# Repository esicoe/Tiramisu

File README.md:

# Tiramisu: a 1000 Hz Hall-effect osu! tablet

Tiramisu is a drawing tablet for [osu!](https://osu.ppy.sh) that tracks a magnet-tipped pen with a grid of
120 Hall-effect sensors and reports its position over USB **1000 times a second**. That's the USB Full-Speed
ceiling, and 7.5x the 133 Hz of a Wacom CTL-472.

It's my independent prototype of the Hall-effect tablet we're building at
[Wonkle](https://github.com/wonkleio). The board and firmware go by **aim1k** in the source.

## Status

| Board | State |
|---|---|
| `tiramisu-dev-RP2354B` | Fabricated and assembled by JLCPCB, brought up, tracking a magnetic pen |
| `tiramisu-dev-CH32V307` | Next revision, in part selection: a RISC-V MCU with built-in USB 2.0 High-Speed to go past 1 kHz |

## Hardware: `tiramisu-dev-RP2354B`

| | |
|---|---|
| MCU | Raspberry Pi RP2354B (dual Arm Cortex-M33, 2 MB in-package flash) |
| Sensors | 120 x HAL403 linear Hall sensors in a 12 x 10 grid at 10 mm pitch |
| Multiplexing | 8 x CD74HC4067 16:1 analog muxes on a shared select bus, one per ADC input |
| PCB | 4 layers, 154 x 147 mm, designed in KiCad |
| Interface | USB-C (Full-Speed): HID plus an optional CDC debug console. SWD header for debugging |

## How it works

- **Scan (core 1).** DMA-driven round-robin over all 120 sensors at about 1.8 kHz per full frame, keeping a
  baseline and a noise sigma for every sensor. A warm-up conversion pass removes the crosstalk that the
  multiplexers' on-resistance causes in the ADC's sample-and-hold.
- **Solve (core 0).** Detects the pen from per-sensor noise thresholds and spatial coherence, seeds a position
  from the centroid, then refines x, y and hover height with a Levenberg-Marquardt fit of a magnetic dipole. A
  1-Euro filter smooths the output without adding lag during fast flicks.
- **Report.** 1 kHz USB HID, paced by the host's polling. The device exposes two collections: an absolute mouse
  that works with no driver, and a vendor-defined collection for [OpenTabletDriver](https://opentabletdriver.net).

The [firmware README](tiramisu-dev-RP2354B/firmware/README.md) covers the solver, the tuning decisions and how
to test without hardware. The [sensing calculations](tiramisu-dev-RP2354B/docs/CALCULATIONS.md) cover grid
geometry, scan-rate budget and magnet choice.

## Repository layout

```
tiramisu-dev-RP2354B/
  pcb/               KiCad project: schematic and 4-layer layout
  manufacturing/     Gerbers, BOM and pick-and-place files for JLCPCB
  firmware/          C firmware on the Pico SDK and TinyUSB
  scripts/           Python host tools
  opentabletdriver/  OpenTabletDriver tablet config and report parser
  docs/              Sensing and scan-rate calculations
  datasheets/
tiramisu-dev-CH32V307/   Next revision (datasheets so far)
images/                  Photos and renders for this README
```

## Build and flash

The build uses the Raspberry Pi Pico SDK. The Pico VS Code extension installs the SDK, the Arm toolchain, CMake
and Ninja in one go.

```powershell
cd tiramisu-dev-RP2354B/firmware
.\build.ps1           # configure (first time) and build
.\build.ps1 -Clean    # wipe build/ and reconfigure
```

Hold **BOOTSEL**, plug the board in, and copy `build/aim1k.uf2` onto the drive that appears.

## Host tools

All of these are Python 3 with no third-party packages. The USB tools use Windows APIs.

| Script | What it does |
|---|---|
| `scripts/grid_view.py` | Live heatmap of the sensor grid over the debug console, plus noise, raw, baseline and recalibrate views |
| `scripts/rate_test.py` | Measures the real HID report rate and its jitter at the host |
| `scripts/set_mode.py` | Turns the driverless mouse collection on or off |
| `scripts/gen_sensor_map.py` | Regenerates the firmware's sensor map straight from the KiCad PCB |

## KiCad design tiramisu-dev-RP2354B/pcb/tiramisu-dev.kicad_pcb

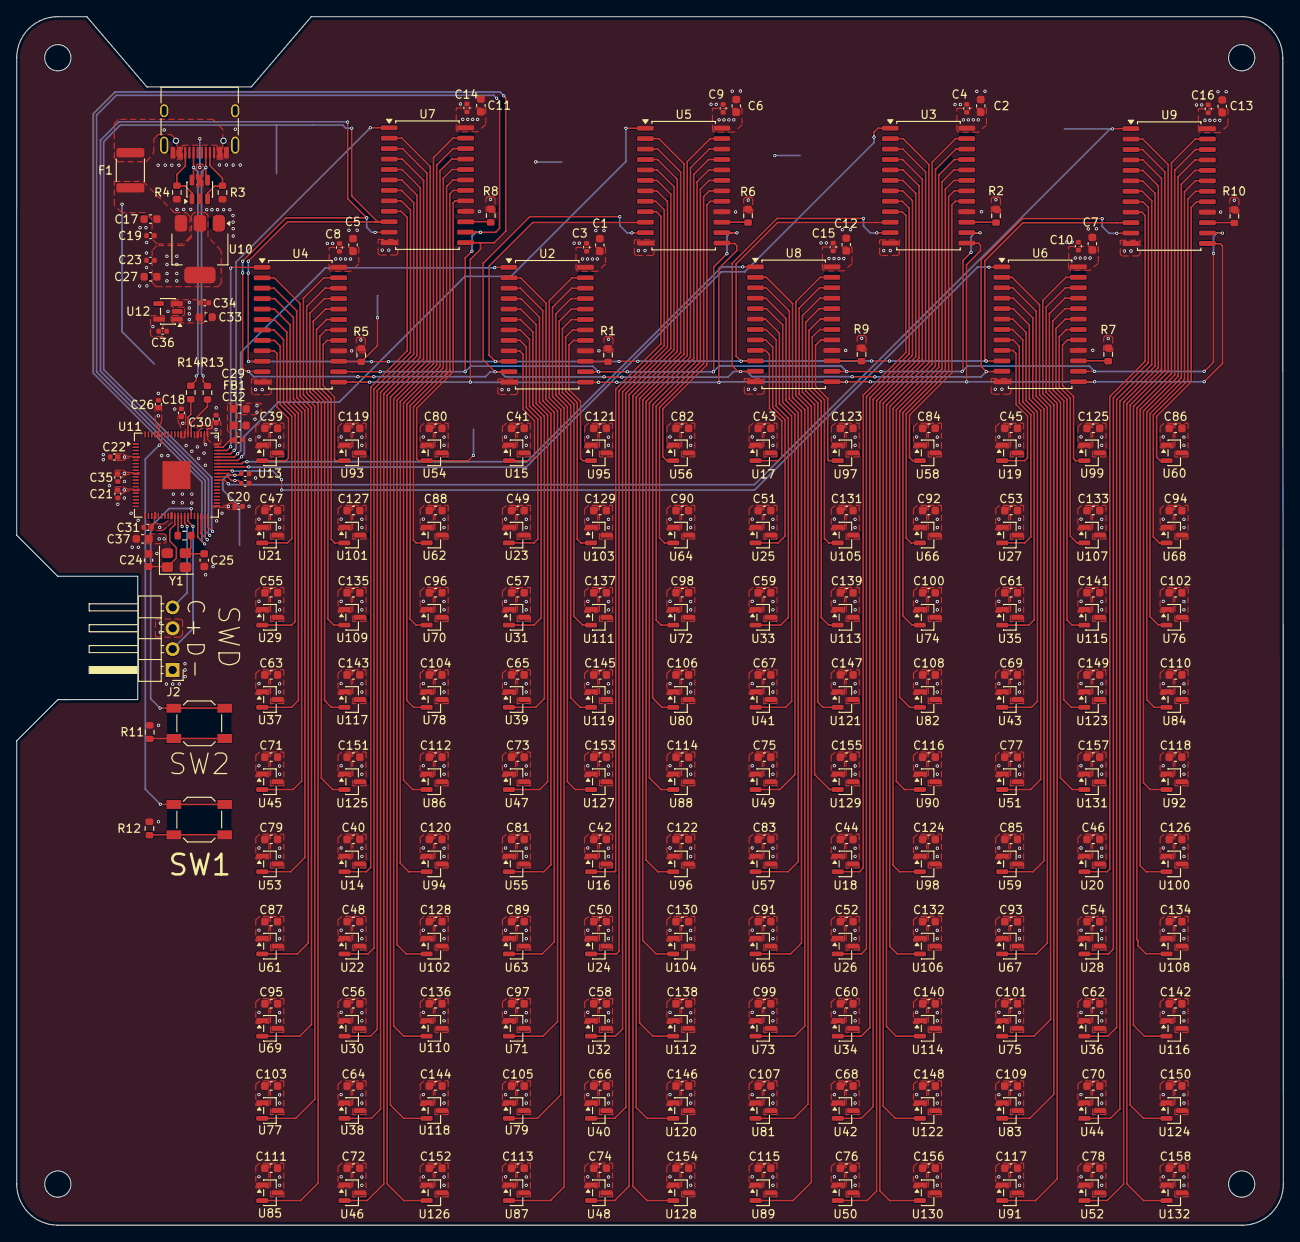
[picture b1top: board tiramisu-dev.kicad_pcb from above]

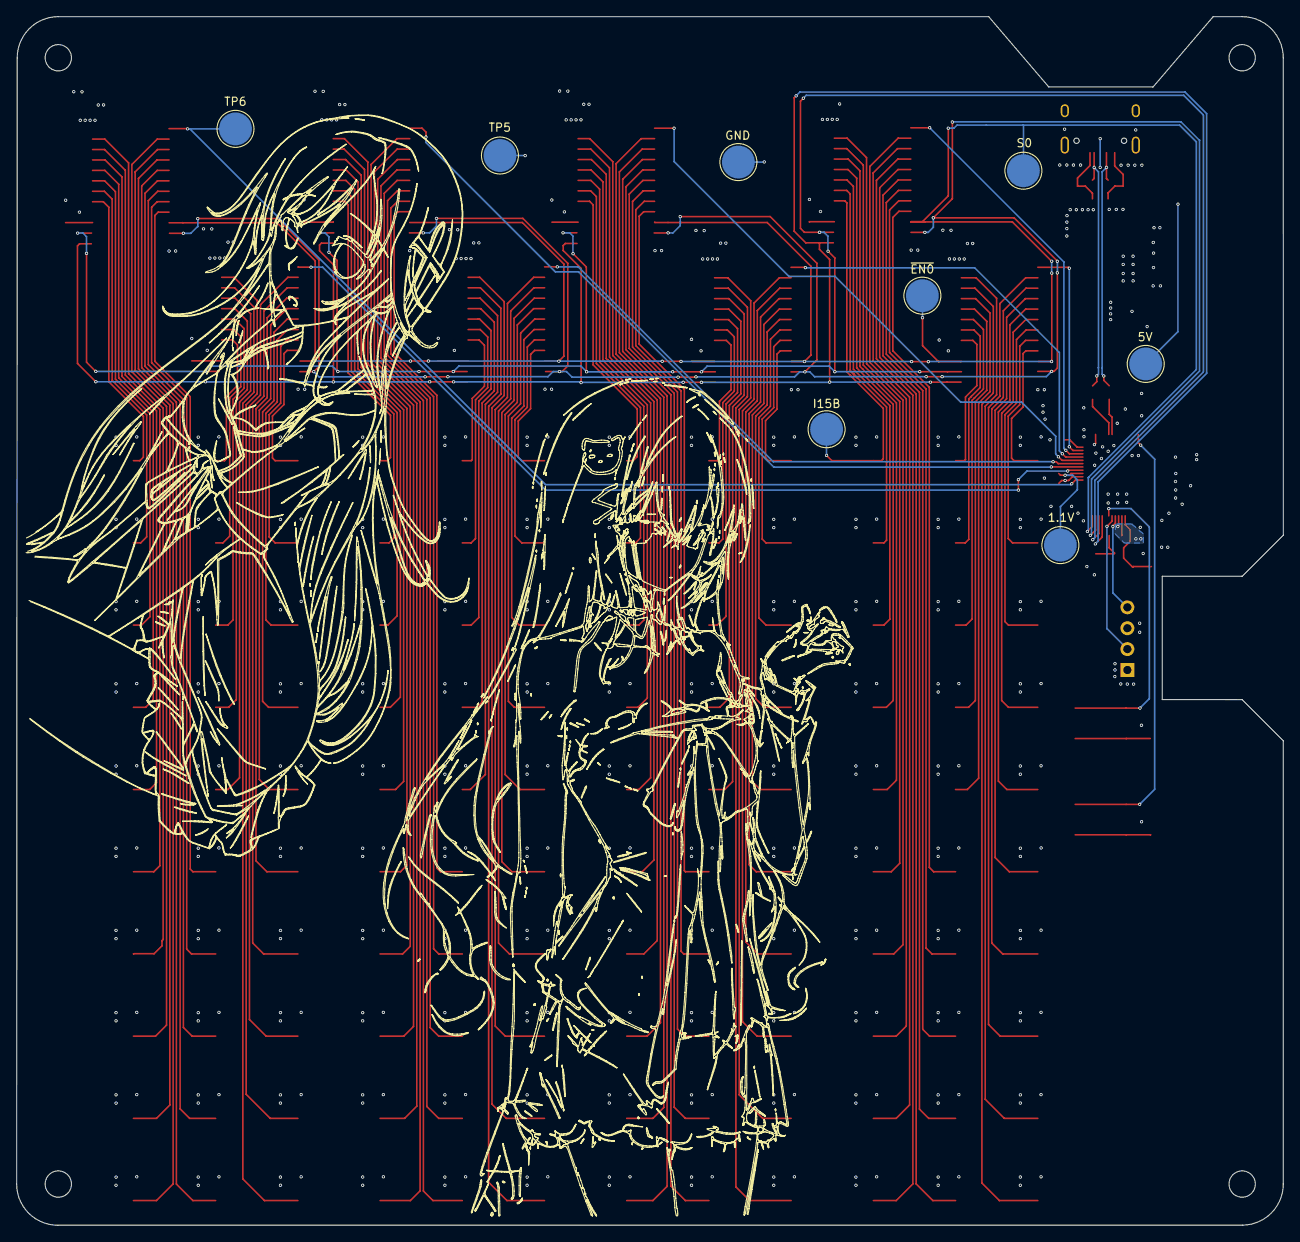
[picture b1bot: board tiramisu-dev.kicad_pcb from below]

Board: 4 copper layers, 154.1 x 147.0 mm, 324 parts (8 on the bottom side), 161 nets.

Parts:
C1, C2, C5, C6, C7, C11, C12, C13, C33: 1u; C_0603_1608Metric
C3, C4, C8, C9, C10, C14, C15, C16, C18, C19, C20, C21, C22, C23, C26, C28, C30, C31, C32, C34, C35, C36, C38: 100n; C_0402_1005Metric
C17: 10u; C_0603_1608Metric
C24, C25: 15p; C_0603_1608Metric
C27: 22u; C_0603_1608Metric
C29, C37: 4u7; C_0603_1608Metric
C39, C40, C41, C42, C43, C44, C45, C46, C47, C48, C49, C50, C51, C52, C53, C54, C55, C56, C57, C58, C59, C60, C61, C62, C63, C64, C65, C66, C67, C68, C69, C70, C71, C72, C73, C74, C75, C76, C77, C78, C79, C80, C81, C82, C83, C84, C85, C86, C87, C88, C89, C90, C91, C92, C93, C94, C95, C96, C97, C98, C99, C100, C101, C102, C103, C104, C105, C106, C107, C108, C109, C110, C111, C112, C113, C114, C115, C116, C117, C118, C119, C120, C121, C122, C123, C124, C125, C126, C127, C128, C129, C130, C131, C132, C133, C134, C135, C136, C137, C138, C139, C140, C141, C142, C143, C144, C145, C146, C147, C148, C149, C150, C151, C152, C153, C154, C155, C156, C157, C158: 0.1u; C_0603_1608Metric
F1: SMD1812P075TF/24; Fuse_1812_4532Metric
FB1: GZ1608D601TF; L_0603_1608Metric
H1, H2, H3, H4: MountingHole; MountingHole_3.2mm_M3
J1: TYPE-C-31-M-12; USB_C_Receptacle_HRO_TYPE-C-31-M-12
J2: SWD; PinHeader_1x04_P2.54mm_Horizontal
R1, R2, R5, R6, R7, R8, R9, R10: 10K; R_0603_1608Metric
R3, R4: 5.1K; R_0603_1608Metric
R11, R12, R15: 1K; R_0603_1608Metric
R13, R14: 27R; R_0603_1608Metric
SW1, SW2: TS-1187A-B-A-B; SW_SPST_SKQG_WithStem
TP1: GND; TestPoint_Pad_D4.0mm
TP2: ~{EN0}; TestPoint_Pad_D4.0mm
TP3: I15B; TestPoint_Pad_D4.0mm
TP4: 5V; TestPoint_Pad_D4.0mm
TP5: 3V3; TestPoint_Pad_D4.0mm
TP6: ADC0; TestPoint_Pad_D4.0mm
TP7: 1V1; TestPoint_Pad_D4.0mm
TP8: S0; TestPoint_Pad_D4.0mm
U1: SRV05-4; SOT-23-6
U2, U3, U4, U5, U6, U7, U8, U9: CD74HC4067M; SOIC-24W_7.5x15.4mm_P1.27mm
U10: AMS1117-3.3; SOT-223-3_TabPin2
U11: RP2354B; QFN-80-1EP_10x10mm_P0.4mm_EP3.4x3.4mm
U12: TLV73311PDBV; SOT-23-5
U13, U14, U15, U16, U17, U18, U19, U20, U21, U22, U23, U24, U25, U26, U27, U28, U29, U30, U31, U32, U33, U34, U35, U36, U37, U38, U39, U40, U41, U42, U43, U44, U45, U46, U47, U48, U49, U50, U51, U52, U53, U54, U55, U56, U57, U58, U59, U60, U61, U62, U63, U64, U65, U66, U67, U68, U69, U70, U71, U72, U73, U74, U75, U76, U77, U78, U79, U80, U81, U82, U83, U84, U85, U86, U87, U88, U89, U90, U91, U92, U93, U94, U95, U96, U97, U98, U99, U100, U101, U102, U103, U104, U105, U106, U107, U108, U109, U110, U111, U112, U113, U114, U115, U116, U117, U118, U119, U120, U121, U122, U123, U124, U125, U126, U127, U128, U129, U130, U131, U132: HAL403SO; SOT-23
Y1: ABM8-272-T3; Crystal_SMD_3225-4Pin_3.2x2.5mm

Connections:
1.1V: C35.1, C36.1, C37.1, C38.1, TP7.1 (1_1), U11.10 (DVDD), U11.32 (DVDD), U11.51 (DVDD), U12.5 (OUT)
3.3V: C1.1, C2.1, C3.1, C4.1, C5.1, C6.1, C7.1, C8.1, C9.1, C10.1, C11.1, C12.1, C13.1, C14.1, C15.1, C16.1, C18.1, C20.1, C21.1, C22.1, C23.1, C26.1, C27.1, C28.1, C30.1, C31.1, C33.1, C34.1, C39.1, C40.1, C41.1, C42.1, C43.1, C44.1, C45.1, C46.1, C47.1, C48.1, C49.1, C50.1, C51.1, C52.1, C53.1, C54.1, C55.1, C56.1, C57.1, C58.1, C59.1, C60.1, C61.1, C62.1, C63.1, C64.1, C65.1, C66.1, C67.1, C68.1, C69.1, C70.1, C71.1, C72.1, C73.1, C74.1, C75.1, C76.1, C77.1, C78.1, C79.1, C80.1, C81.1, C82.1, C83.1, C84.1, C85.1, C86.1, C87.1, C88.1, C89.1, C90.1, C91.1, C92.1, C93.1, C94.1, C95.1, C96.1, C97.1, C98.1, C99.1, C100.1, C101.1, C102.1, C103.1, C104.1, C105.1, C106.1, C107.1, C108.1, C109.1, C110.1, C111.1, C112.1, C113.1, C114.1, C115.1, C116.1, C117.1, C118.1, C119.1, C120.1, C121.1, C122.1, C123.1, C124.1, C125.1, C126.1, C127.1, C128.1, C129.1, C130.1, C131.1, C132.1, C133.1, C134.1, C135.1, C136.1, C137.1, C138.1, C139.1, C140.1, C141.1, C142.1, C143.1, C144.1, C145.1, C146.1, C147.1, C148.1, C149.1, C150.1, C151.1, C152.1, C153.1, C154.1, C155.1, C156.1, C157.1, C158.1, FB1.1, J2.3, TP5.1 (1_1), U2.24 (VCC), U3.24 (VCC), U4.24 (VCC), U5.24 (VCC), U6.24 (VCC), U7.24 (VCC), U8.24 (VCC), U9.24 (VCC), U10.2 (VO), U11.5 (IOVDD), U11.15 (IOVDD), U11.24 (IOVDD), U11.29 (IOVDD), U11.41 (IOVDD), U11.50 (IOVDD), U11.60 (IOVDD), U11.61 (VREG_AVDD), U11.64 (VREG_VIN), U11.68 (USB_OTP_VDD), U11.69 (QSPI_IOVDD), U11.76 (IOVDD), U12.1 (IN), U12.3 (EN), U13.1 (VCC), U14.1 (VCC), U15.1 (VCC), U16.1 (VCC), U17.1 (VCC), U18.1 (VCC), U19.1 (VCC), U20.1 (VCC), U21.1 (VCC), U22.1 (VCC), U23.1 (VCC), U24.1 (VCC), U25.1 (VCC), U26.1 (VCC), U27.1 (VCC), U28.1 (VCC), U29.1 (VCC), U30.1 (VCC), U31.1 (VCC), U32.1 (VCC), U33.1 (VCC), U34.1 (VCC), U35.1 (VCC), U36.1 (VCC), U37.1 (VCC), U38.1 (VCC), U39.1 (VCC), U40.1 (VCC), U41.1 (VCC), U42.1 (VCC), U43.1 (VCC), U44.1 (VCC), U45.1 (VCC), U46.1 (VCC), U47.1 (VCC), U48.1 (VCC), U49.1 (VCC), U50.1 (VCC), U51.1 (VCC), U52.1 (VCC), U53.1 (VCC), U54.1 (VCC), U55.1 (VCC), U56.1 (VCC), U57.1 (VCC), U58.1 (VCC), U59.1 (VCC), U60.1 (VCC), U61.1 (VCC), U62.1 (VCC), U63.1 (VCC), U64.1 (VCC), U65.1 (VCC), U66.1 (VCC), U67.1 (VCC), U68.1 (VCC), U69.1 (VCC), U70.1 (VCC), U71.1 (VCC), U72.1 (VCC), U73.1 (VCC), U74.1 (VCC), U75.1 (VCC), U76.1 (VCC), U77.1 (VCC), U78.1 (VCC), U79.1 (VCC), U80.1 (VCC), U81.1 (VCC), U82.1 (VCC), U83.1 (VCC), U84.1 (VCC), U85.1 (VCC), U86.1 (VCC), U87.1 (VCC), U88.1 (VCC), U89.1 (VCC), U90.1 (VCC), U91.1 (VCC), U92.1 (VCC), U93.1 (VCC), U94.1 (VCC), U95.1 (VCC), U96.1 (VCC), U97.1 (VCC), U98.1 (VCC), U99.1 (VCC), U100.1 (VCC), U101.1 (VCC), U102.1 (VCC), U103.1 (VCC), U104.1 (VCC), U105.1 (VCC), U106.1 (VCC), U107.1 (VCC), U108.1 (VCC), U109.1 (VCC), U110.1 (VCC), U111.1 (VCC), U112.1 (VCC), U113.1 (VCC), U114.1 (VCC), U115.1 (VCC), U116.1 (VCC), U117.1 (VCC), U118.1 (VCC), U119.1 (VCC), U120.1 (VCC), U121.1 (VCC), U122.1 (VCC), U123.1 (VCC), U124.1 (VCC), U125.1 (VCC), U126.1 (VCC), U127.1 (VCC), U128.1 (VCC), U129.1 (VCC), U130.1 (VCC), U131.1 (VCC), U132.1 (VCC)
/CC1: J1.A5 (CC1), R3.2, U1.3 (IO2)
/CC2: J1.B5 (CC2), R4.2, U1.1 (IO1)
/S0: TP8.1 (1_1), U2.10 (S0), U3.10 (S0), U4.10 (S0), U5.10 (S0), U6.10 (S0), U7.10 (S0), U8.10 (S0), U9.10 (S0), U11.40 (GPIO32)
/S1: U2.11 (S1), U3.11 (S1), U4.11 (S1), U5.11 (S1), U6.11 (S1), U7.11 (S1), U8.11 (S1), U9.11 (S1), U11.39 (GPIO31)
/S2: U2.14 (S2), U3.14 (S2), U4.14 (S2), U5.14 (S2), U6.14 (S2), U7.14 (S2), U8.14 (S2), U9.14 (S2), U11.38 (GPIO30)
/S3: U2.13 (S3), U3.13 (S3), U4.13 (S3), U5.13 (S3), U6.13 (S3), U7.13 (S3), U8.13 (S3), U9.13 (S3), U11.37 (GPIO29)
ADC0: U4.1 (COM), U11.58 (GPIO47/ADC7)
ADC1: U7.1 (COM), U11.57 (GPIO46/ADC6)
ADC2: U2.1 (COM), U11.56 (GPIO45/ADC5)
ADC3: U5.1 (COM), U11.55 (GPIO44/ADC4)
ADC4: U8.1 (COM), U11.54 (GPIO43/ADC3)
ADC5: U3.1 (COM), U11.53 (GPIO42/ADC2)
ADC6: U6.1 (COM), U11.52 (GPIO41/ADC1)
ADC7: TP6.1 (1_1), U9.1 (COM), U11.49 (GPIO40/ADC0)
D+: J1.B6 (D+), R14.1, U1.6 (IO4)
D-: J1.B7 (D-), R13.2, U1.4 (IO3)
GND: C1.2, C2.2, C3.2, C4.2, C5.2, C6.2, C7.2, C8.2, C9.2, C10.2, C11.2, C12.2, C13.2, C14.2, C15.2, C16.2, C17.2, C18.2, C19.2, C20.2, C21.2, C22.2, C23.2, C24.1, C25.2, C26.2, C27.2, C28.2, C29.2, C30.2, C31.2, C32.2, C33.2, C34.2, C35.2, C36.2, C37.2, C38.2, C39.2, C40.2, C41.2, C42.2, C43.2, C44.2, C45.2, C46.2, C47.2, C48.2, C49.2, C50.2, C51.2, C52.2, C53.2, C54.2, C55.2, C56.2, C57.2, C58.2, C59.2, C60.2, C61.2, C62.2, C63.2, C64.2, C65.2, C66.2, C67.2, C68.2, C69.2, C70.2, C71.2, C72.2, C73.2, C74.2, C75.2, C76.2, C77.2, C78.2, C79.2, C80.2, C81.2, C82.2, C83.2, C84.2, C85.2, C86.2, C87.2, C88.2, C89.2, C90.2, C91.2, C92.2, C93.2, C94.2, C95.2, C96.2, C97.2, C98.2, C99.2, C100.2, C101.2, C102.2, C103.2, C104.2, C105.2, C106.2, C107.2, C108.2, C109.2, C110.2, C111.2, C112.2, C113.2, C114.2, C115.2, C116.2, C117.2, C118.2, C119.2, C120.2, C121.2, C122.2, C123.2, C124.2, C125.2, C126.2, C127.2, C128.2, C129.2, C130.2, C131.2, C132.2, C133.2, C134.2, C135.2, C136.2, C137.2, C138.2, C139.2, C140.2, C141.2, C142.2, C143.2, C144.2, C145.2, C146.2, C147.2, C148.2, C149.2, C150.2, C151.2, C152.2, C153.2, C154.2, C155.2, C156.2, C157.2, C158.2, J1.A1 (GND), J1.A12 (GND), J1.B1 (GND), J1.B12 (GND), J1.SH (SHIELD), J2.1, R1.1, R2.1, R3.1, R4.1, R5.1, R6.1, R7.1, R8.1, R9.1, R10.1, R11.2, R12.2, TP1.1 (1_1), U1.2 (VN), U2.12 (GND), U2.16 (I15), U3.12 (GND), U3.16 (I15), U4.12 (GND), U4.16 (I15), U5.12 (GND), U5.16 (I15), U6.12 (GND), U6.16 (I15), U7.12 (GND), U7.16 (I15), U8.12 (GND), U8.16 (I15), U9.12 (GND), U9.16 (I15), U10.1 (GND), U11.62 (VREG_PGND), U11.65 (VREG_FB), U11.81 (GND), U12.2 (GND), U13.3 (GND), U14.3 (GND), U15.3 (GND), U16.3 (GND), U17.3 (GND), U18.3 (GND), U19.3 (GND), U20.3 (GND), U21.3 (GND), U22.3 (GND), U23.3 (GND), U24.3 (GND), U25.3 (GND), U26.3 (GND), U27.3 (GND), U28.3 (GND), U29.3 (GND), U30.3 (GND), U31.3 (GND), U32.3 (GND), U33.3 (GND), U34.3 (GND), U35.3 (GND), U36.3 (GND), U37.3 (GND), U38.3 (GND), U39.3 (GND), U40.3 (GND), U41.3 (GND), U42.3 (GND), U43.3 (GND), U44.3 (GND), U45.3 (GND), U46.3 (GND), U47.3 (GND), U48.3 (GND), U49.3 (GND), U50.3 (GND), U51.3 (GND), U52.3 (GND), U53.3 (GND), U54.3 (GND), U55.3 (GND), U56.3 (GND), U57.3 (GND), U58.3 (GND), U59.3 (GND), U60.3 (GND), U61.3 (GND), U62.3 (GND), U63.3 (GND), U64.3 (GND), U65.3 (GND), U66.3 (GND), U67.3 (GND), U68.3 (GND), U69.3 (GND), U70.3 (GND), U71.3 (GND), U72.3 (GND), U73.3 (GND), U74.3 (GND), U75.3 (GND), U76.3 (GND), U77.3 (GND), U78.3 (GND), U79.3 (GND), U80.3 (GND), U81.3 (GND), U82.3 (GND), U83.3 (GND), U84.3 (GND), U85.3 (GND), U86.3 (GND), U87.3 (GND), U88.3 (GND), U89.3 (GND), U90.3 (GND), U91.3 (GND), U92.3 (GND), U93.3 (GND), U94.3 (GND), U95.3 (GND), U96.3 (GND), U97.3 (GND), U98.3 (GND), U99.3 (GND), U100.3 (GND), U101.3 (GND), U102.3 (GND), U103.3 (GND), U104.3 (GND), U105.3 (GND), U106.3 (GND), U107.3 (GND), U108.3 (GND), U109.3 (GND), U110.3 (GND), U111.3 (GND), U112.3 (GND), U113.3 (GND), U114.3 (GND), U115.3 (GND), U116.3 (GND), U117.3 (GND), U118.3 (GND), U119.3 (GND), U120.3 (GND), U121.3 (GND), U122.3 (GND), U123.3 (GND), U124.3 (GND), U125.3 (GND), U126.3 (GND), U127.3 (GND), U128.3 (GND), U129.3 (GND), U130.3 (GND), U131.3 (GND), U132.3 (GND), Y1.2 (G), Y1.4 (G)
I0A: U4.9 (I0), U13.2 (OUT)
I0B: U7.9 (I0), U14.2 (OUT)
I0C: U2.9 (I0), U15.2 (OUT)
I0D: U5.9 (I0), U16.2 (OUT)
I0E: U8.9 (I0), U17.2 (OUT)
I0F: U3.9 (I0), U18.2 (OUT)
I0G: U6.9 (I0), U19.2 (OUT)
I0H: U9.9 (I0), U20.2 (OUT)
I1A: U4.8 (I1), U21.2 (OUT)
I1B: U7.8 (I1), U22.2 (OUT)
I1C: U2.8 (I1), U23.2 (OUT)
I1D: U5.8 (I1), U24.2 (OUT)
I1E: U8.8 (I1), U25.2 (OUT)
I1F: U3.8 (I1), U26.2 (OUT)
I1G: U6.8 (I1), U27.2 (OUT)
I1H: U9.8 (I1), U28.2 (OUT)
I2A: U4.7 (I2), U29.2 (OUT)
I2B: U7.7 (I2), U30.2 (OUT)
I2C: U2.7 (I2), U31.2 (OUT)
I2D: U5.7 (I2), U32.2 (OUT)
I2E: U8.7 (I2), U33.2 (OUT)
I2F: U3.7 (I2), U34.2 (OUT)
I2G: U6.7 (I2), U35.2 (OUT)
I2H: U9.7 (I2), U36.2 (OUT)
I3A: U4.6 (I3), U37.2 (OUT)
I3B: U7.6 (I3), U38.2 (OUT)
I3C: U2.6 (I3), U39.2 (OUT)
I3D: U5.6 (I3), U40.2 (OUT)
I3E: U8.6 (I3), U41.2 (OUT)
I3F: U3.6 (I3), U42.2 (OUT)
I3G: U6.6 (I3), U43.2 (OUT)
I3H: U9.6 (I3), U44.2 (OUT)
I4A: U4.5 (I4), U45.2 (OUT)
I4B: U7.5 (I4), U46.2 (OUT)
I4C: U2.5 (I4), U47.2 (OUT)
I4D: U5.5 (I4), U48.2 (OUT)
I4E: U8.5 (I4), U49.2 (OUT)
I4F: U3.5 (I4), U50.2 (OUT)
I4G: U6.5 (I4), U51.2 (OUT)
I4H: U9.5 (I4), U52.2 (OUT)
I5A: U4.4 (I5), U53.2 (OUT)
I5B: TP3.1 (1_1), U7.17 (I14), U54.2 (OUT)
I5C: U2.4 (I5), U55.2 (OUT)
I5D: U5.17 (I14), U56.2 (OUT)
I5E: U8.4 (I5), U57.2 (OUT)
I5F: U3.17 (I14), U58.2 (OUT)
I5G: U6.4 (I5), U59.2 (OUT)
I5H: U9.17 (I14), U60.2 (OUT)
I6A: U4.3 (I6), U61.2 (OUT)
I6B: U7.18 (I13), U62.2 (OUT)
I6C: U2.3 (I6), U63.2 (OUT)
I6D: U5.18 (I13), U64.2 (OUT)
I6E: U8.3 (I6), U65.2 (OUT)
I6F: U3.18 (I13), U66.2 (OUT)
I6G: U6.3 (I6), U67.2 (OUT)
I6H: U9.18 (I13), U68.2 (OUT)
I7A: U4.2 (I7), U69.2 (OUT)
I7B: U7.19 (I12), U70.2 (OUT)
I7C: U2.2 (I7), U71.2 (OUT)
I7D: U5.19 (I12), U72.2 (OUT)
I7E: U8.2 (I7), U73.2 (OUT)
I7F: U3.19 (I12), U74.2 (OUT)
I7G: U6.2 (I7), U75.2 (OUT)
I7H: U9.19 (I12), U76.2 (OUT)
I8A: U4.23 (I8), U77.2 (OUT)
I8B: U7.20 (I11), U78.2 (OUT)
I8C: U2.23 (I8), U79.2 (OUT)
I8D: U5.20 (I11), U80.2 (OUT)
I8E: U8.23 (I8), U81.2 (OUT)
I8F: U3.20 (I11), U82.2 (OUT)
I8G: U6.23 (I8), U83.2 (OUT)
I8H: U9.20 (I11), U84.2 (OUT)
I9A: U4.22 (I9), U85.2 (OUT)
I9B: U7.21 (I10), U86.2 (OUT)
I9C: U2.22 (I9), U87.2 (OUT)
I9D: U5.21 (I10), U88.2 (OUT)
I9E: U8.22 (I9), U89.2 (OUT)
I9F: U3.21 (I10), U90.2 (OUT)
I9G: U6.22 (I9), U91.2 (OUT)
I9H: U9.21 (I10), U92.2 (OUT)
I10A: U4.17 (I14), U93.2 (OUT)
I10B: U7.22 (I9), U94.2 (OUT)
I10C: U2.17 (I14), U95.2 (OUT)
I10D: U5.22 (I9), U96.2 (OUT)
I10E: U8.17 (I14), U97.2 (OUT)
I10F: U3.22 (I9), U98.2 (OUT)
I10G: U6.17 (I14), U99.2 (OUT)
I10H: U9.22 (I9), U100.2 (OUT)
I11A: U4.18 (I13), U101.2 (OUT)
I11B: U7.23 (I8), U102.2 (OUT)
I11C: U2.18 (I13), U103.2 (OUT)
I11D: U5.23 (I8), U104.2 (OUT)
I11E: U8.18 (I13), U105.2 (OUT)
I11F: U3.23 (I8), U106.2 (OUT)
I11G: U6.18 (I13), U107.2 (OUT)
I11H: U9.23 (I8), U108.2 (OUT)
I12A: U4.19 (I12), U109.2 (OUT)
I12B: U7.2 (I7), U110.2 (OUT)
I12C: U2.19 (I12), U111.2 (OUT)
I12D: U5.2 (I7), U112.2 (OUT)
I12E: U8.19 (I12), U113.2 (OUT)
I12F: U3.2 (I7), U114.2 (OUT)
I12G: U6.19 (I12), U115.2 (OUT)
I12H: U9.2 (I7), U116.2 (OUT)
I13A: U4.20 (I11), U117.2 (OUT)
I13B: U7.3 (I6), U118.2 (OUT)
I13C: U2.20 (I11), U119.2 (OUT)
I13D: U5.3 (I6), U120.2 (OUT)
I13E: U8.20 (I11), U121.2 (OUT)
I13F: U3.3 (I6), U122.2 (OUT)
I13G: U6.20 (I11), U123.2 (OUT)
I13H: U9.3 (I6), U124.2 (OUT)
I14A: U4.21 (I10), U125.2 (OUT)
I14B: U7.4 (I5), U126.2 (OUT)
I14C: U2.21 (I10), U127.2 (OUT)
I14D: U5.4 (I5), U128.2 (OUT)
I14E: U8.21 (I10), U129.2 (OUT)
I14F: U3.4 (I5), U130.2 (OUT)
I14G: U6.21 (I10), U131.2 (OUT)
I14H: U9.4 (I5), U132.2 (OUT)
unnamed: C25.1, R15.1, Y1.3
unnamed: J2.2, U11.34 (SWDIO)
unnamed: J2.4, U11.33 (SWCLK)
unnamed: R11.1, SW2.1
unnamed: R12.1, SW1.1
unnamed: C17.1, C19.1, F1.2, TP4.1 (1_1), U10.3 (VI)
unnamed: C29.1, C32.1, FB1.2, U11.59 (ADC_AVDD)
unnamed: SW2.2, U11.35 (RUN)
unnamed: R13.1, U11.66 (USB_DM)
unnamed: R14.2, U11.67 (USB_DP)
unnamed: C24.2, U11.30 (XIN), Y1.1
unnamed: R15.2, U11.31 (XOUT)
unnamed: SW1.2, U11.75 (~QSPI_SS)
VBUS: F1.1, J1.A4 (VBUS), J1.A9 (VBUS), J1.B4 (VBUS), J1.B9 (VBUS), U1.5 (VP)
~EN0: R5.2, TP2.1 (1_1), U4.15 (~E)
~EN1: R8.2, U7.15 (~E)
~EN2: R1.2, U2.15 (~E)
~EN3: R6.2, U5.15 (~E)
~EN4: R9.2, U8.15 (~E)
~EN5: R2.2, U3.15 (~E)
~EN6: R7.2, U6.15 (~E)
~EN7: R10.2, U9.15 (~E)

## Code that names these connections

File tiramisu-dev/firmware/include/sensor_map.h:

// AUTO-GENERATED by scripts/gen_sensor_map.py from tiramisu-dev.kicad_pcb
// - do not edit by hand. Re-run it whenever the PCB changes.
// 120 x HAL403SO, 12 cols x 10 rows, 10.0 mm pitch.
#pragma once
#include <stdint.h>

#define SENSOR_COLS   12
#define SENSOR_ROWS   10
#define SENSOR_COUNT  120
#define SENSOR_PITCH_MM   10.0f
#define MUX_COUNT     8
#define MUX_CHANNELS  16
#define MUX_USED_CH   15   // channel 15 is tied to GND on every mux

// Mux select lines (shared bus). Enables are tied low in hardware.
#define PIN_SEL_S0  32
#define PIN_SEL_S1  31
#define PIN_SEL_S2  30
#define PIN_SEL_S3  29
#define ADC_GPIO_BASE 40  // ADC input i -> GPIO(40+i)

// grid[adc_input][channel] -> linear sensor index (row*COLS+col),
// 0xFFFF = unused. Indexed by ADC INPUT, so the scanner needs no
// reversal step: the net names ADC0..ADC7 are wired backwards, and
// that is already accounted for here.
static const uint16_t SENSOR_GRID[MUX_COUNT][MUX_CHANNELS] = {
  { 0x0046, 0x0052, 0x005E, 0x006A, 0x0076, 0x0077, 0x006B, 0x005F, 0x0053, 0x0047, 0x003B, 0x002F, 0x0023, 0x0017, 0x000B, 0xFFFF }, // ADC in 0 = GPIO40, U9 (net ADC7)
  { 0x0009, 0x0015, 0x0021, 0x002D, 0x0039, 0x0045, 0x0051, 0x005D, 0x0069, 0x0075, 0x003A, 0x002E, 0x0022, 0x0016, 0x000A, 0xFFFF }, // ADC in 1 = GPIO41, U6 (net ADC6)
  { 0x0043, 0x004F, 0x005B, 0x0067, 0x0073, 0x0074, 0x0068, 0x005C, 0x0050, 0x0044, 0x0038, 0x002C, 0x0020, 0x0014, 0x0008, 0xFFFF }, // ADC in 2 = GPIO42, U3 (net ADC5)
  { 0x0006, 0x0012, 0x001E, 0x002A, 0x0036, 0x0042, 0x004E, 0x005A, 0x0066, 0x0072, 0x0037, 0x002B, 0x001F, 0x0013, 0x0007, 0xFFFF }, // ADC in 3 = GPIO43, U8 (net ADC4)
  { 0x0040, 0x004C, 0x0058, 0x0064, 0x0070, 0x0071, 0x0065, 0x0059, 0x004D, 0x0041, 0x0035, 0x0029, 0x001D, 0x0011, 0x0005, 0xFFFF }, // ADC in 4 = GPIO44, U5 (net ADC3)
  { 0x0003, 0x000F, 0x001B, 0x0027, 0x0033, 0x003F, 0x004B, 0x0057, 0x0063, 0x006F, 0x0034, 0x0028, 0x001C, 0x0010, 0x0004, 0xFFFF }, // ADC in 5 = GPIO45, U2 (net ADC2)
  { 0x003D, 0x0049, 0x0055, 0x0061, 0x006D, 0x006E, 0x0062, 0x0056, 0x004A, 0x003E, 0x0032, 0x0026, 0x001A, 0x000E, 0x0002, 0xFFFF }, // ADC in 6 = GPIO46, U7 (net ADC1)
  { 0x0000, 0x000C, 0x0018, 0x0024, 0x0030, 0x003C, 0x0048, 0x0054, 0x0060, 0x006C, 0x0031, 0x0025, 0x0019, 0x000D, 0x0001, 0xFFFF }, // ADC in 7 = GPIO47, U4 (net ADC0)
};

static inline float sensor_x_mm(int idx){ return (idx % SENSOR_COLS) * SENSOR_PITCH_MM; }
static inline float sensor_y_mm(int idx){ return (idx / SENSOR_COLS) * SENSOR_PITCH_MM; }
